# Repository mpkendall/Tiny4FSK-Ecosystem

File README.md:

# Tiny4FSK Ecosystem

### A set of additional features, tools, and boards to expand functionality of Tiny4FSK

### TinyShield
TinyShield is an expansion board which sits atop of Tiny4FSK's expansion pins. It adds:
1. An OLED screen for basic flight diagnostics,
2. SD card for logging,
3. 5v logic headers for more sensors,
4. Integrated buck/boost for wider range of power sources, including a LiPo connector,
5. Qwiic headers for adding more sensors!

Code in the Tiny4FSK repository already implements automatic sensor, SD card, and screen scanning and initialization. Functions pertaining to these features are configurable in both `config.h` and the main `Tiny4FSK.ino` file.

To get started, solder female headers to the 2.54mm pins on the back side of the shield. To interface with the Tiny4FSK board, additionally solder 2.54mm male header rows to the USB, power, and data headers on the Tiny4FSK. Mounting them for alignment may assist with soldering.

Insert the shield board onto the Tiny4FSK's headers as shown. No code changes are required to continue with SD card logging and screen initialization.

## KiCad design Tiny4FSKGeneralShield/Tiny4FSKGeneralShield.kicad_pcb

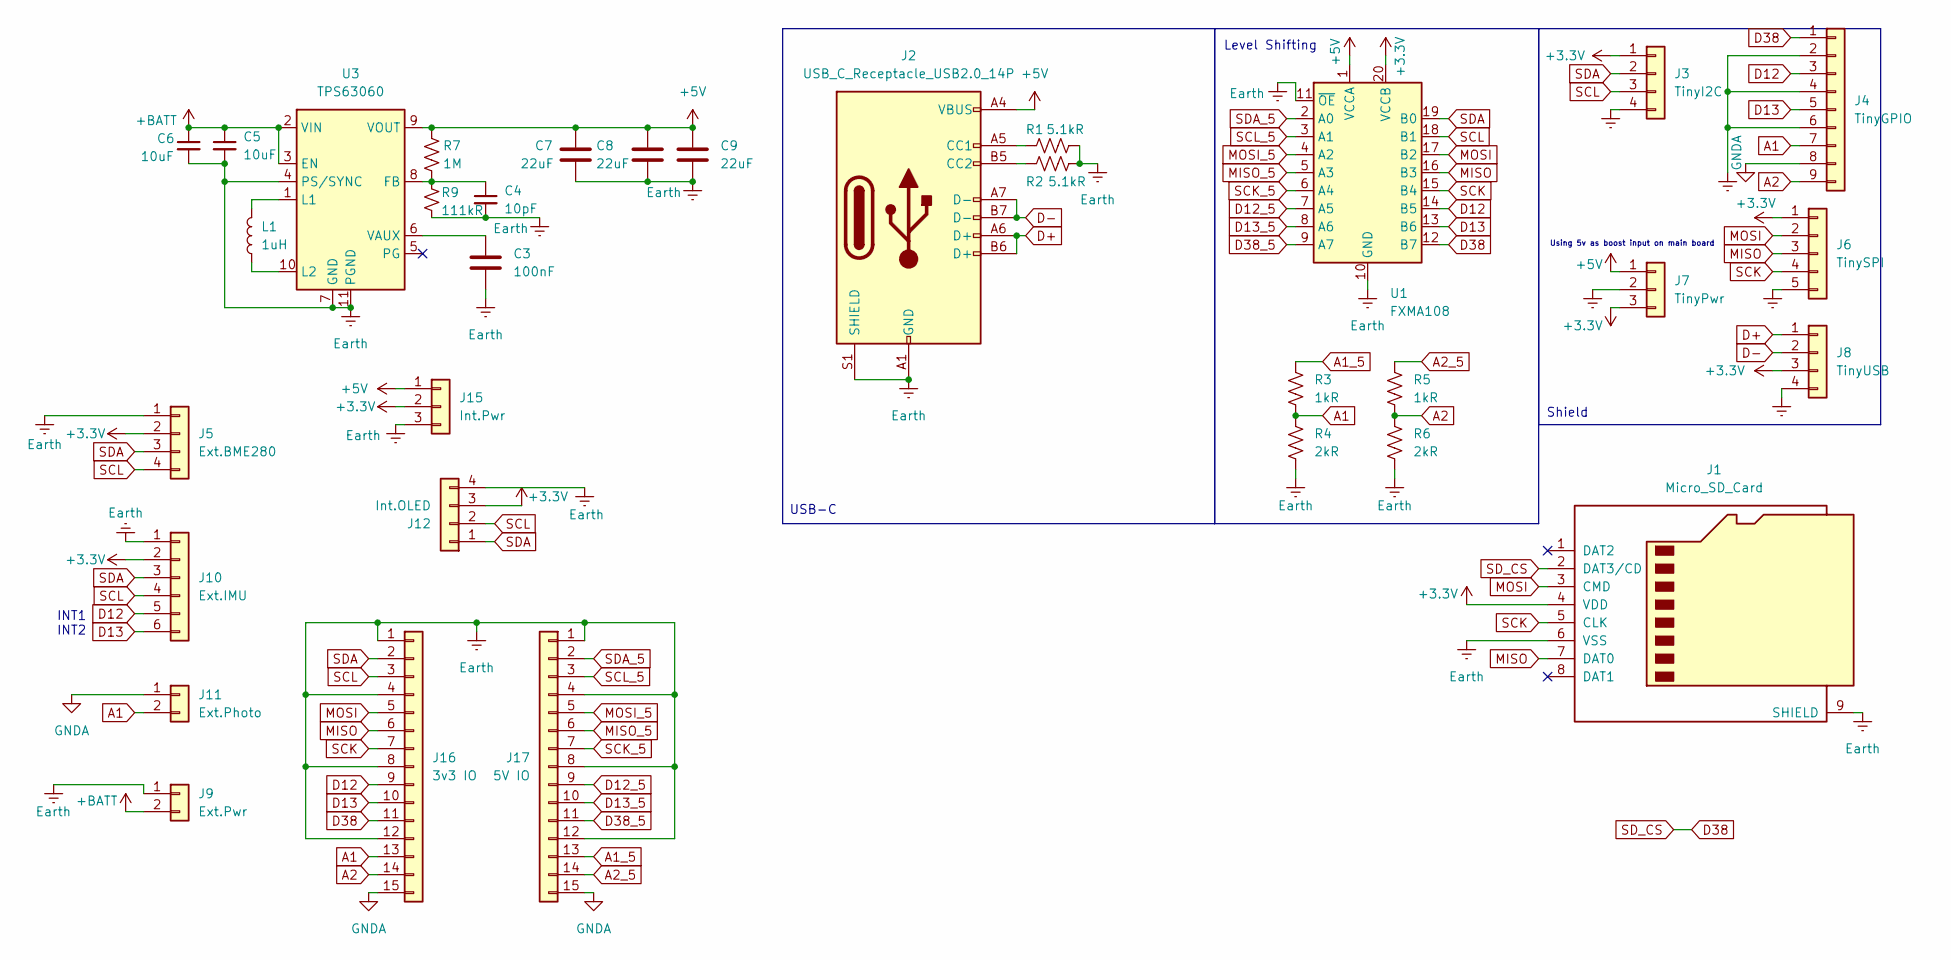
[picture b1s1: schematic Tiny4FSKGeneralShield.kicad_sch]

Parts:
C3: 100nF; C_0402_1005Metric; JLCPCB Part # C1525
C4: 10pF; C_0402_1005Metric; JLCPCB Part # C32949
C5, C6: 10uF; C_0402_1005Metric; JLCPCB Part # C15525
C7, C8, C9: 22uF; C_0603_1608Metric; JLCPCB Part # C59461
J1: Micro_SD_Card; microSD_HC_Hirose_DM3D-SF; JLCPCB Part # C719027
J2: USB_C_Receptacle_USB2.0_14P; USB_C_Receptacle_GCT_USB4105-xx-A_16P_TopMnt_Horizontal; JLCPCB Part # C2760486
J3: TinyI2C; PinSocket_1x04_P2.54mm_Vertical
J4: TinyGPIO; PinSocket_1x09_P2.54mm_Vertical
J5: Ext.BME280; JST_SH_SM04B-SRSS-TB_1x04-1MP_P1.00mm_Horizontal; JLCPCB Part # C51940130
J6: TinySPI; PinSocket_1x05_P2.54mm_Vertical
J7: TinyPwr; PinSocket_1x03_P2.54mm_Vertical
J8: TinyUSB; PinSocket_1x04_P2.54mm_Vertical
J9: Ext.Pwr; HX20007-2AWB; JLCPCB Part # C442222
J10: Ext.IMU; JST_SH_SM06B-SRSS-TB_1x06-1MP_P1.00mm_Horizontal; JLCPCB Part # C160405
J11: Ext.Photo; JST_SH_SM02B-SRSS-TB_1x02-1MP_P1.00mm_Horizontal; JLCPCB Part # C160402
J12: Int.OLED; PinHeader_1x04_P2.54mm_Vertical
J15: Int.Pwr; PinHeader_1x03_P2.54mm_Vertical
J16: 3v3 IO; PinHeader_1x15_P2.54mm_Vertical
J17: 5V IO; PinHeader_1x15_P2.54mm_Vertical
L1: 1uH; IND_SRP4020FA-1R0M; JLCPCB Part # C842935
R1, R2: 5.1kR; R_0402_1005Metric; JLCPCB Part # C25905
R3, R5: 1kR; R_0402_1005Metric; JLCPCB Part # C11702
R4, R6: 2kR; R_0402_1005Metric; JLCPCB Part # C4109
R7: 1M; R_0402_1005Metric; JLCPCB Part # C26083
R9: 111kR; R_0805_2012Metric; JLCPCB Part # C865144
U1: FXMA108; WQFN-20-1EP_2.5x4.5mm_P0.5mm_EP1x2.9mm; JLCPCB Part # C891320
U3: TPS63060; Texas_S-PWSON-N10_ThermalVias; JLCPCB Part # C48567

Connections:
+3.3V: J1.4 (VDD), J3.1, J5.2, J6.1, J7.3, J8.3, J10.2, J12.3, J15.2, U1.20 (VCCB)
+5V: C7.1, C8.1, C9.1, J2.A4 (VBUS), J2.A9 (VBUS), J2.B4 (VBUS), J2.B9 (VBUS), J7.1, J15.1, R7.1, U1.1 (VCCA), U3.9 (VOUT)
+BATT: C5.1, C6.1, J9.2, U3.2 (VIN), U3.3 (EN)
A1: J4.7, J11.2, J16.13, R3.2, R4.1
A1_5: J17.13, R3.1
A2: J4.9, J16.14, R5.2, R6.1
A2_5: J17.14, R5.1
D12: J4.3, J10.5, J16.9, U1.14 (B5)
D12_5: J17.9, U1.7 (A5)
D13: J4.5, J10.6, J16.10, U1.13 (B6)
D13_5: J17.10, U1.8 (A6)
D38: J1.2 (DAT3/CD), J4.1, J16.11, U1.12 (B7)
D38_5: J17.11, U1.9 (A7)
D+: J2.A6 (D+), J2.B6 (D+), J8.1
D-: J2.A7 (D-), J2.B7 (D-), J8.2
Earth: C3.2, C4.2, C5.2, C6.2, C7.2, C8.2, C9.2, J1.6 (VSS), J1.9 (SHIELD), J2.A1 (GND), J2.A12 (GND), J2.B1 (GND), J2.B12 (GND), J2.S1 (SHIELD), J3.4, J4.2, J4.4, J4.6, J5.1, J6.5, J7.2, J8.4, J9.1, J10.1, J12.4, J15.3, J16.1, J16.4, J16.8, J16.12, J17.1, J17.4, J17.8, J17.12, R1.2, R2.2, R4.2, R6.2, R9.2, U1.10 (GND), U1.11 (~OE), U3.4 (PS/SYNC), U3.7 (GND), U3.11 (PGND)
GNDA: J4.8, J11.1, J16.15, J17.15
MISO: J1.7 (DAT0), J6.3, J16.6, U1.16 (B3)
MISO_5: J17.6, U1.5 (A3)
MOSI: J1.3 (CMD), J6.2, J16.5, U1.17 (B2)
MOSI_5: J17.5, U1.4 (A2)
unnamed: J2.A5 (CC1), R1.1
unnamed: J2.B5 (CC2), R2.1
unnamed: C4.1, R7.2, R9.1, U3.8 (FB)
unnamed: L1.2, U3.1 (L1)
unnamed: L1.1, U3.10 (L2)
unnamed: C3.1, U3.6 (VAUX)
SCK: J1.5 (CLK), J6.4, J16.7, U1.15 (B4)
SCK_5: J17.7, U1.6 (A4)
SCL: J3.3, J5.4, J10.4, J12.2, J16.3, U1.18 (B1)
SCL_5: J17.3, U1.3 (A1)
SDA: J3.2, J5.3, J10.3, J12.1, J16.2, U1.19 (B0)
SDA_5: J17.2, U1.2 (A0)

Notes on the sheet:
Level Shifting
USB-C
INT1 INT2
Using 5v as boost input on main board
Shield

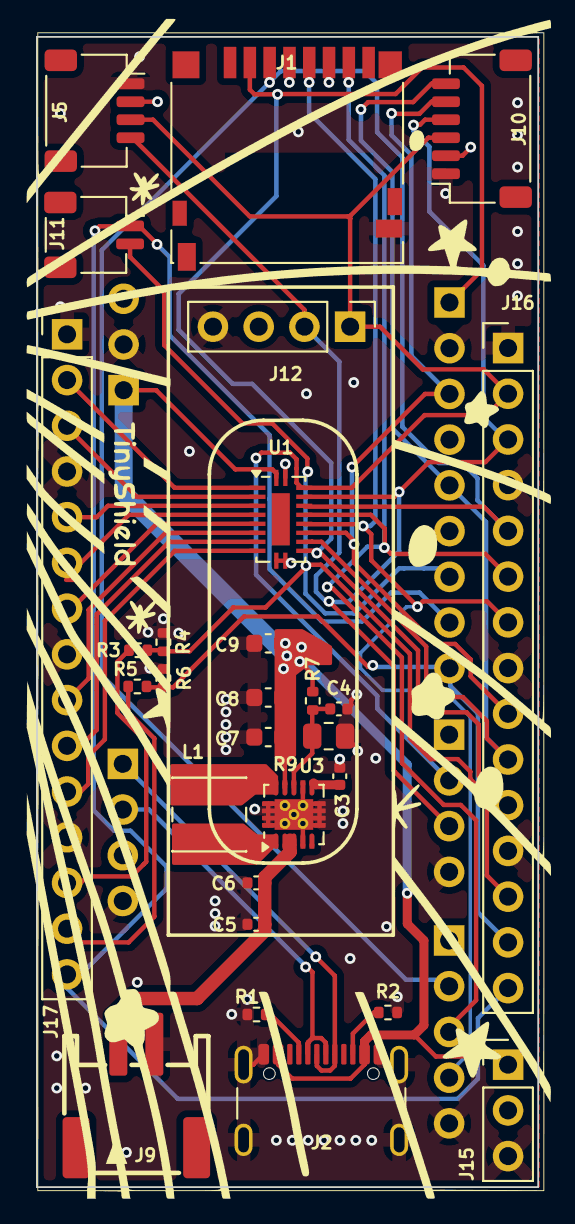
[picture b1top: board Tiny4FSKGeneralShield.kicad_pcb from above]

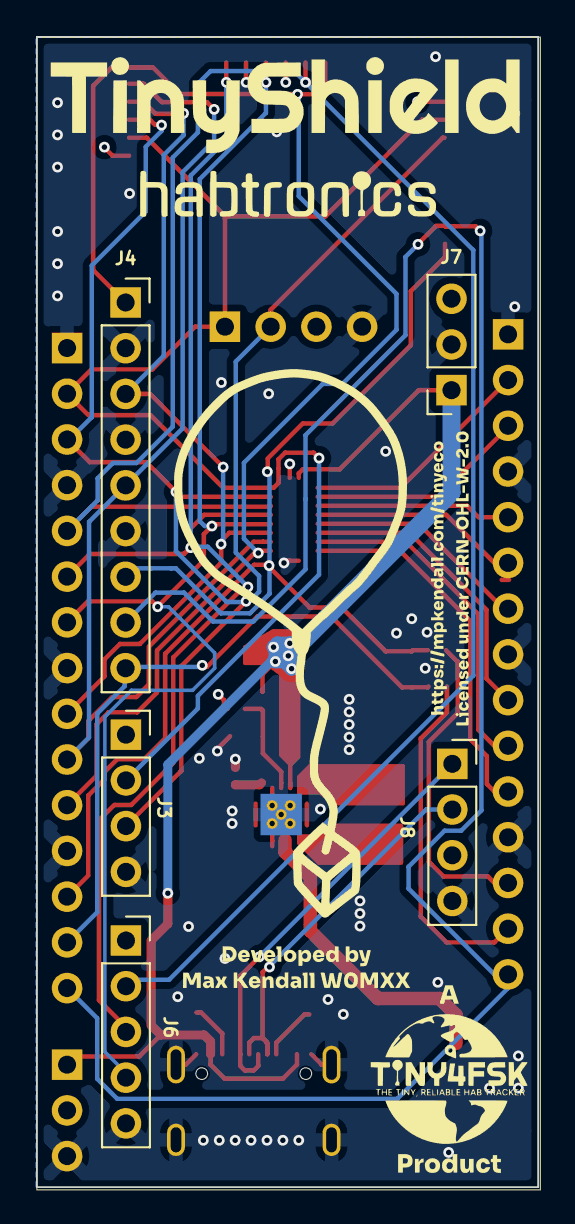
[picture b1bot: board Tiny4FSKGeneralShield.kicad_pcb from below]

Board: 4 copper layers, 27.9 x 63.9 mm, 33 parts (5 on the bottom side), 33 nets.

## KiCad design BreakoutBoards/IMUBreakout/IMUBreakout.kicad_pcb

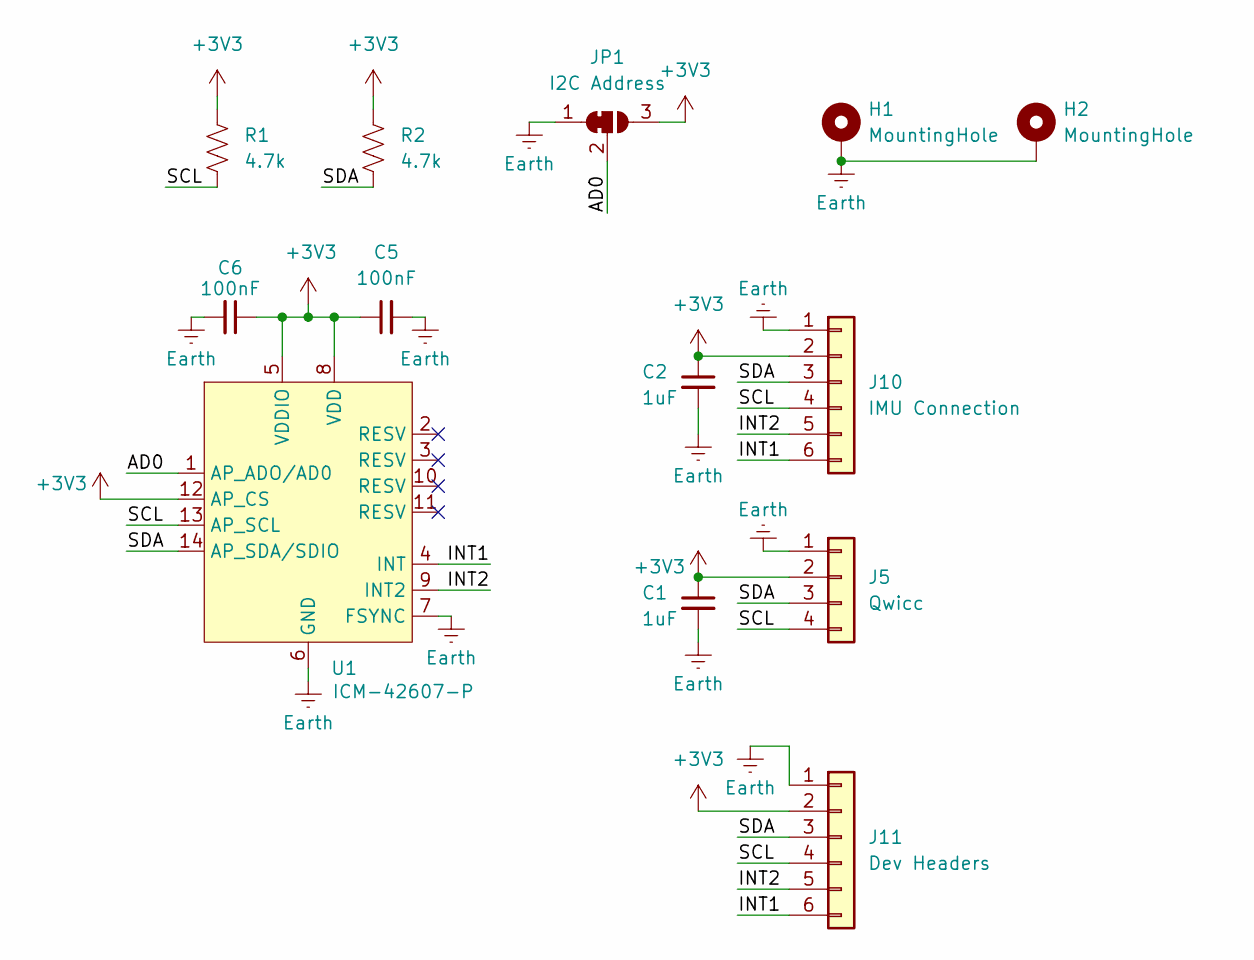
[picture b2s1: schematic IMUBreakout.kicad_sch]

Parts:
C1, C2: 1uF; C_0402_1005Metric; LCSC C52923
C5, C6: 100nF; C_0402_1005Metric; LCSC C1525
H1, H2: MountingHole; MountingHole_2.2mm_M2_Pad_Via
J5: Qwicc; JST_SH_SM04B-SRSS-TB_1x04-1MP_P1.00mm_Horizontal; LCSC C51940130
J10: IMU Connection; JST_SH_SM06B-SRSS-TB_1x06-1MP_P1.00mm_Horizontal; LCSC C160405
J11: Dev Headers; PinSocket_1x06_P2.54mm_Vertical
JP1: I2C Address; SolderJumper-3_P1.3mm_Bridged12_RoundedPad1.0x1.5mm
R1, R2: 4.7k; R_0402_1005Metric; LCSC C25900
U1: ICM-42607-P; Bosch_LGA-14_3x2.5mm_P0.5mm; LCSC C5129967

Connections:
+3V3: C1.1, C2.1, C5.1, C6.1, J5.2, J10.2, J11.2, JP1.3 (B), R1.1, R2.1, U1.5 (VDDIO), U1.8 (VDD), U1.12 (AP_CS)
/AD0: JP1.2 (C), U1.1 (AP_ADO/AD0)
/INT1: J10.6, J11.6, U1.4 (INT)
/INT2: J10.5, J11.5, U1.9 (INT2)
/SCL: J5.4, J10.4, J11.4, R1.2, U1.13 (AP_SCL)
/SDA: J5.3, J10.3, J11.3, R2.2, U1.14 (AP_SDA/SDIO)
Earth: C1.2, C2.2, C5.2, C6.2, H1.1, H2.1, J5.1, J10.1, J11.1, JP1.1 (A), U1.6 (GND), U1.7 (FSYNC)

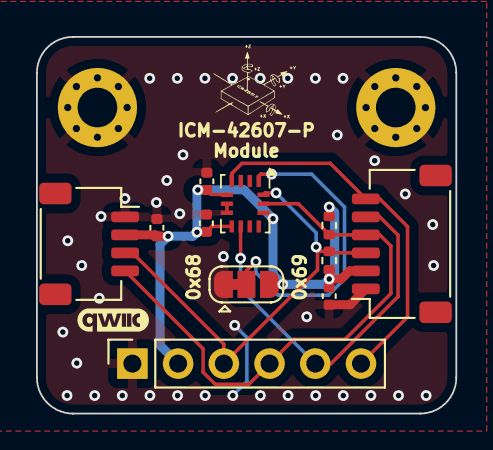
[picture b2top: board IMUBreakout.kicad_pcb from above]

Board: 2 copper layers, 23.3 x 20.9 mm, 13 parts (0 on the bottom side), 7 nets.

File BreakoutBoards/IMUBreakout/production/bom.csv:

Designator,Footprint,Quantity,Value,LCSC Part #
"C1, C2",0402,2,1uF,C52923
"C5, C6",0402,2,100nF,C1525
J10,JST_SH_SM06B-SRSS-TB_1x06-1MP_P1.00mm_Horizontal,1,IMU Connection,C160405
J5,JST_SH_SM04B-SRSS-TB_1x04-1MP_P1.00mm_Horizontal,1,Qwicc,C51940130
"R1, R2",0402,2,4.7k,C25900
U1,Bosch_LGA-14_3x2.5mm_P0.5mm,1,ICM-42607-P,C5129967

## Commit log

2025-11-03 ugh it got overwritten
2025-11-04 starting to get caught up
2025-11-11 need to find jlc part for qwiic
2025-11-13 release candidate!
2026-01-04 update pcb
2026-01-12 updated IMU board and production files
2026-01-12 documentation!
2026-01-12 gitignore update
2026-03-23 kicad 10
2026-03-23 new pics :eyes:
2026-03-23 / not \
